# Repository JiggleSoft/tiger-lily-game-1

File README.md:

# Tiger-Lily's Game 1

## Introduction

This is an implementation of an electronic reaction game built with the Microchip PIC16F15323 MCU.
All work is performed by Tiger-Lily under the supervision of her father.

## Game

### UI

FIXME
FIXME
FIXME
FIXME
FIXME

 * On / Off Power Switch
 * 3 x LED (Red, Yellow, Green, Blue)
 * 2 x Push Button Switches (e, Yellow, Green, Blue)
 * Start Push Button
 * Longest Sequence Push Button
 * Game Selection Sliding Switch (3 position)
  1 = Repeat
  2 = Player Adds
  3 = Elimination
 * Level Selection Sliding Switch (4 position)
  1 = 8 Sequence Length
  2 = 14 Sequence Length
  3 = 20 Sequence Length
  4 = 31 Sequence Length
 * PWM Controlled Sounder
 * Internal
  * Reset Button
  * ICSP Programming / Debug Header

### Game

TODO: describe the game.

#### Notes

TODO: !!!

## Microcontroller

### Summary

Microchip PIC16F15323-I/P or -E/P Microcontroller.
 * TODO

### Game Pin ALlocation

TODO: !!!!!!!!!!1

| Pin | Signal      | Allocation               |
| --- | ----------- | ------------------------ |
|   1 | Vdd         | Positive 4.5 - 5.0 Volts |
|   2 | RA5         | SW Skill 2               |
|   3 | RA4         | SW Skill 1               |
|   4 | -MCLR/VPP   | Reset and programming    |
|   5 | RC5         | LED 2 (YELLOW)           |
|   6 | RC4         | LED 1 (RED)              |
|   7 | RC3         | Sounder                  |
|   8 | RC6         | LED 3 (GREEN)            |
|   9 | RC7         | LED 4 (BLUE)             |
|  10 | RB7         | SW 4 (BLUE)              |
|  11 | RB6         | SW 3 (GREEN)             |
|  12 | RB5         | SW 2 (YELLOW)            |
|  13 | RB4         | SW 1  (RED)              |
|  14 | RC2         | SW Level 3               |
|  15 | RC1         | SW Level 2               |
|  16 | RC0         | SW Level 1               |
|  17 | RA2         | SW Start                 |
|  18 | RA1/ICSPCLK | SW Longest               |
|  19 | RA0/ICSPDAT | SW Last                  |
|  20 | Vss         | Ground                   |

ONLY 14 PINS !!!!!!!!!!!

Note that only the used signals are shown and other signals may be available on the pins.

## Licensing

Copyright (C) 2021 Justin Lane.
All rights reserved.

This repository, projects, and contents are Copyright (C) 2021 Justin Lane and are released under the Solderpad Hardware License 2.1.
This is a liberal open-source license derived from the Apache License Version 2.0.
Please see the [LICENSE](LICENSE) file for more details.

## Contact Us

Please email tigerlilygame1@jigglesoft.co.uk regarding this repository.

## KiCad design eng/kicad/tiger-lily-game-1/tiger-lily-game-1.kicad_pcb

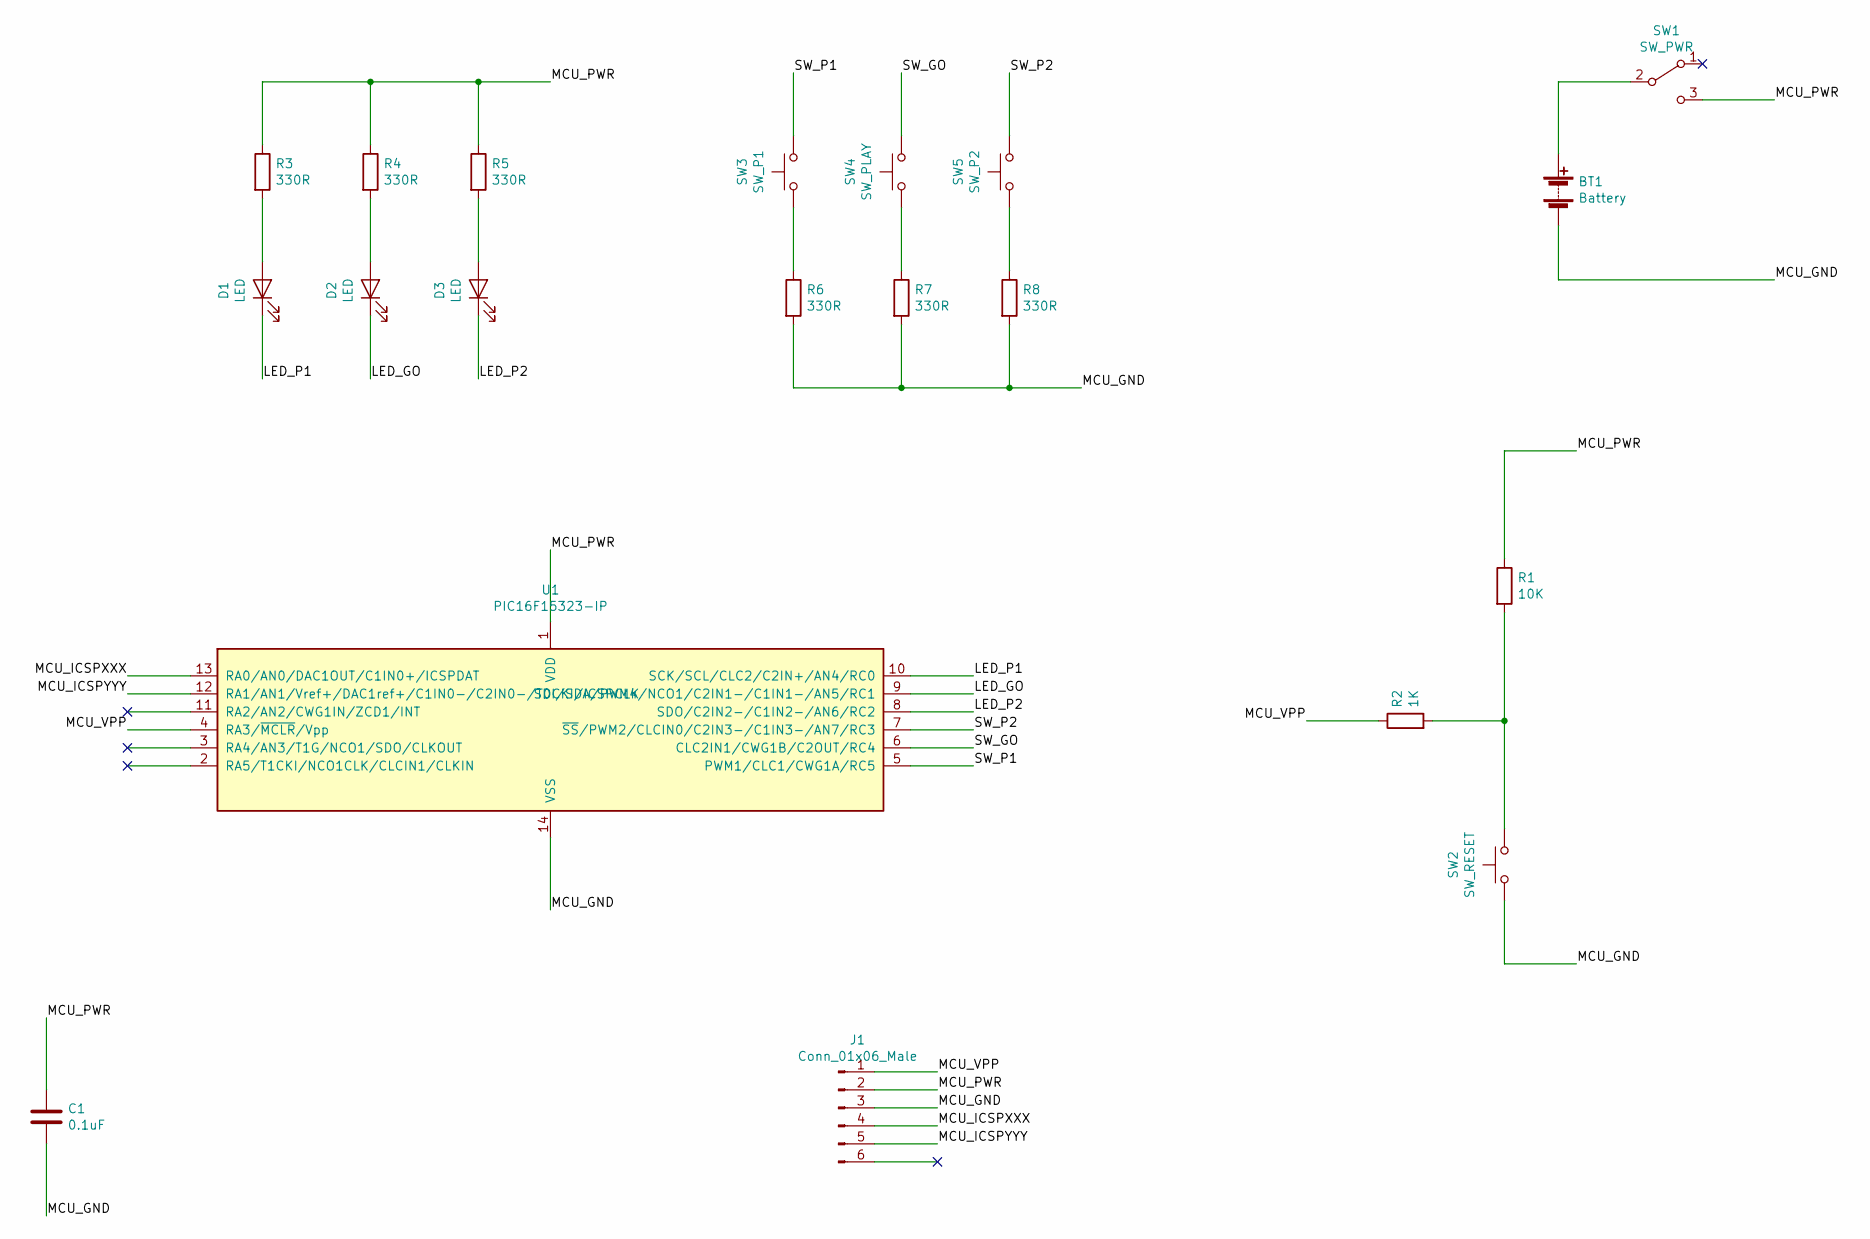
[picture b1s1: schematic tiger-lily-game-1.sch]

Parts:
BT1: Battery; BatteryHolder_Keystone_2479_3xAAA
C1: 0.1uF; C_Disc_D3.0mm_W2.0mm_P2.50mm
D1, D2, D3: LED; LED_D5.0mm
J1: Conn_01x06_Male; PinHeader_1x06_P2.54mm_Horizontal
R1: 10K; R_Axial_DIN0204_L3.6mm_D1.6mm_P7.62mm_Horizontal
R2: 1K; R_Axial_DIN0204_L3.6mm_D1.6mm_P7.62mm_Horizontal
R3, R4, R5, R6, R7, R8: 330R; R_Axial_DIN0204_L3.6mm_D1.6mm_P7.62mm_Horizontal
SW1: SW_PWR; SW_CuK_OS102011MA1QN1_SPDT_Angled
SW2: SW_RESET; SW_PUSH_6mm
SW3: SW_P1; SW_PUSH_6mm
SW4: SW_PLAY; SW_PUSH_6mm
SW5: SW_P2; SW_PUSH_6mm
U1: PIC16F15323-IP; DIP-14_W7.62mm

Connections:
/LED_GO: D2.1 (K), U1.9 (SDI/SDA/PWM4/NCO1/C2IN1-/C1IN1-/AN5/RC1)
/LED_P1: D1.1 (K), U1.10 (SCK/SCL/CLC2/C2IN+/AN4/RC0)
/LED_P2: D3.1 (K), U1.8 (SDO/C2IN2-/C1IN2-/AN6/RC2)
/MCU_GND: BT1.2 (-), C1.2, J1.3, R6.2, R7.2, R8.2, SW2.1, U1.14 (VSS)
/MCU_ICSPXXX: J1.4, U1.13 (RA0/AN0/DAC1OUT/C1IN0+/ICSPDAT)
/MCU_ICSPYYY: J1.5, U1.12 (RA1/AN1/Vref+/DAC1ref+/C1IN0-/C2IN0-/T0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)
/MCU_PWR: C1.1, J1.2, R1.1, R3.1, R4.1, R5.1, SW1.3 (C), U1.1 (VDD)
/MCU_VPP: J1.1, R2.1, U1.4 (RA3/~MCLR~/Vpp)
/SW_GO: SW4.2, U1.6 (CLC2IN1/CWG1B/C2OUT/RC4)
/SW_P1: SW3.2, U1.5 (PWM1/CLC1/CWG1A/RC5)
/SW_P2: SW5.2, U1.7 (~SS~/PWM2/CLCIN0/C2IN3-/C1IN3-/AN7/RC3)
unnamed: BT1.1 (+), SW1.2 (B)
unnamed: D1.2 (A), R3.2
unnamed: D2.2 (A), R4.2
unnamed: D3.2 (A), R5.2
unnamed: R1.2, R2.2, SW2.2
unnamed: R6.1, SW3.1
unnamed: R7.1, SW4.1
unnamed: R8.1, SW5.1

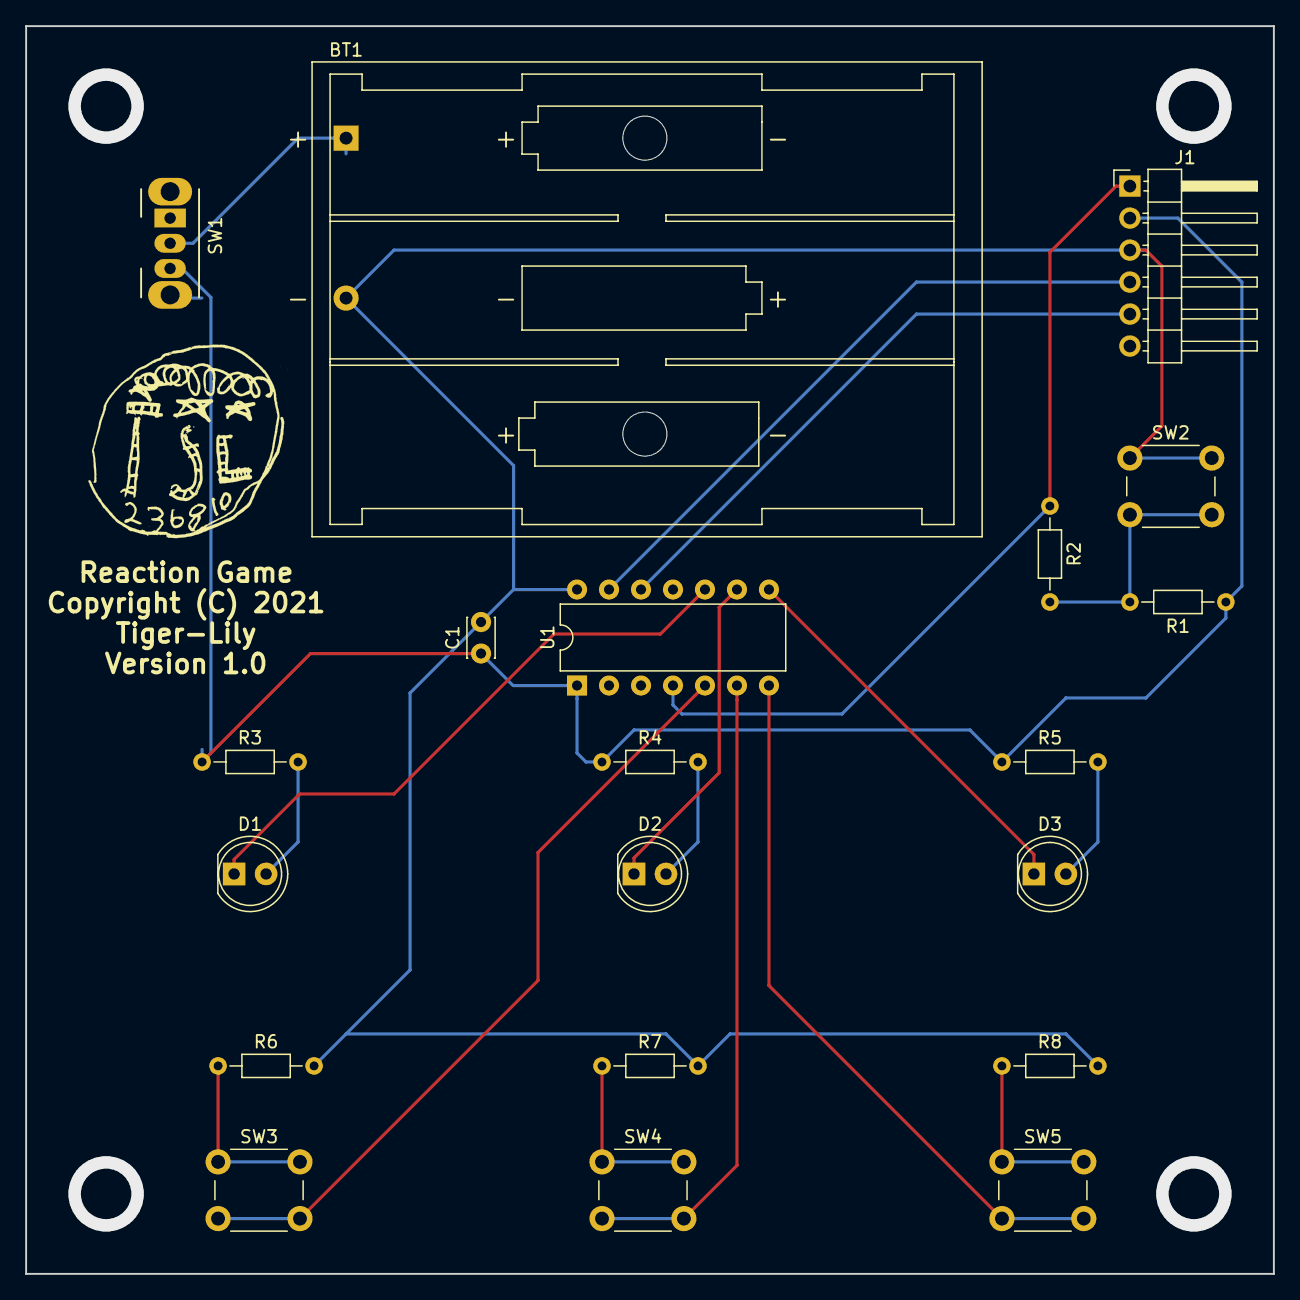
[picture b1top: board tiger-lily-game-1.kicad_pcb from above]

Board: 2 copper layers, 99.1 x 99.1 mm, 20 parts (0 on the bottom side), 19 nets.

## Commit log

2021-10-24 Initial commit of README.md, .gitignore, LICENSE files along with initial skeleton schematic and PCB layout.
2021-10-24 Changed MCU to PIC16F15323 as simpler, cheaper, and available. Added custom schematic for MCU as not in library installed. Tried PCB layout (do not like it so will change). Added skeleton firmware pr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
2021-11-05 Added TSL logo library.
2021-11-10 Schematic and PCB design (WIP). Firmware (WIP). Checked in for backup.
2021-11-15 Candidate Schematic and PCB. TODO: Check silkscreen text.
